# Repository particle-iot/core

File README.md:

The Spark Core
=====

These are the hardware design files for the Spark Core, developed by Hex Labs, Inc. dba Spark.

These files have been made available online through a [Creative Commons Attribution-ShareAlike 3.0](http://creativecommons.org/licenses/by-sa/3.0/) license.

You are welcome to distribute, remix, and use these files for commercial purposes. If you do so, please attribute the original design to Spark both on the website and on the physical packaging of the product or in the instruction manual. All derivative works must be published under the same or a similar license.

## The Story

Development of the Spark Core in its current form began in January 2013 in Shenzhen, China during Spark's participation in the HAXLR8R hardware accelerator.  Development of the Spark Cloud was started in December 2011 as software infrastructure to support the Spark Socket.  Between January and May of 2013, the Spark Core and Cloud were developed from prototypes to a functional platform for building internet-connected hardware.  On May 2, 2013, the Spark Core was launched on the crowdfunding platform Kickstarter.  On May 17, 2013, the hardware design files for the product were released here on GitHub for others to use and learn from.

## What's Included

**BOM** — Current bill of materials for the latestversion of the Spark Core.  Includes part number labels from design files, component values, quantities, and package types.

**Datasheets** — Datasheets for the various components included on the Spark Core, including the STM32F103CBT6 microcontroller and the CC3000 Wi-Fi module.

**EAGLE** — Schematic and board files for the Spark Core.  We use EAGLE, a freemium PCB design software package, for the design and development of the Spark Core.

**Gerber** — Complete set of Gerber files for the current version of the Core.  Use these files to spin up and assemble your own Cores!

**Libraries** — EAGLE libraries for the components used on the Spark Core.

**PDFs** — Includes detailed description of component placement on the Core (especially useful during assembly).  Also includes mechanical drawings and a detailed schematic of the Core for reference and debugging.

**Pin Mapping** — Detailed pin mapping of the Spark Core and STM32, providing information about which pins are mapped to which peripherals.

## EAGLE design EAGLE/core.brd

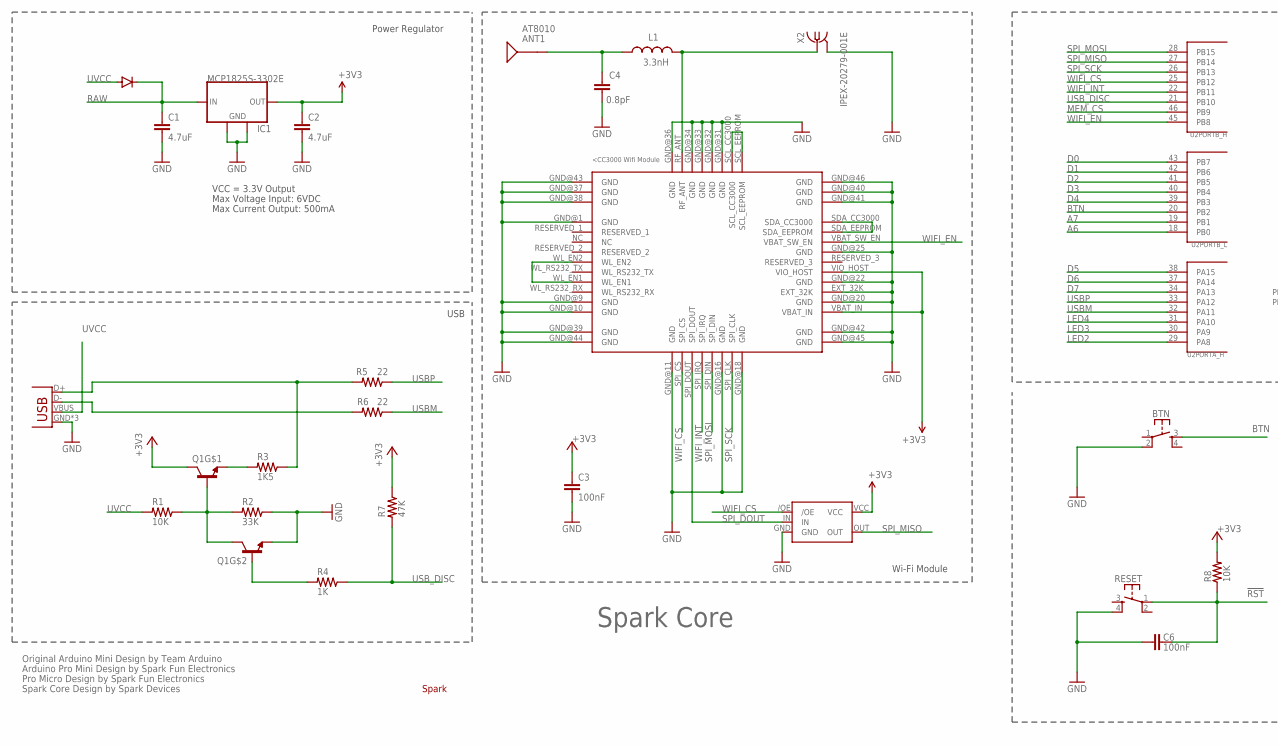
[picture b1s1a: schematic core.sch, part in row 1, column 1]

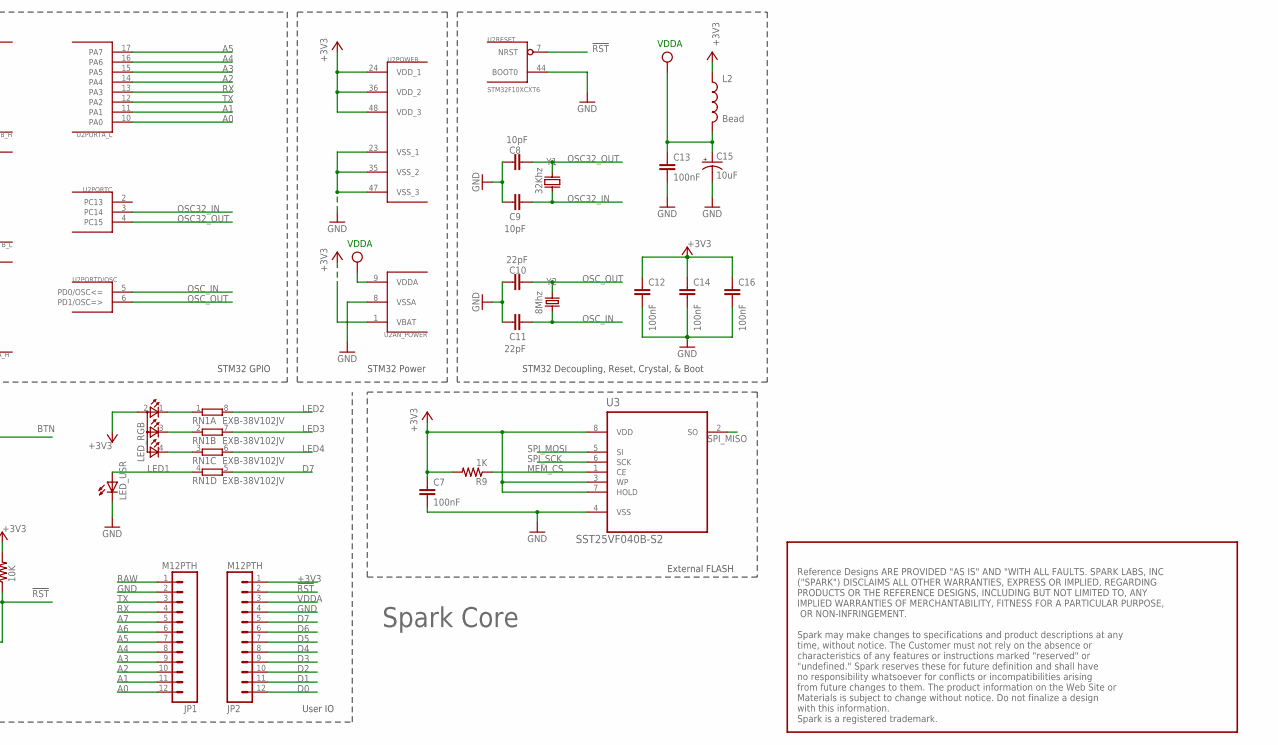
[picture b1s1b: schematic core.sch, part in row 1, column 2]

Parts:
ANT1: AT8010
BTN: KMR211GLFS; TACTILE_SWITCH_SMD
C1, C2: 4.7uF; C0603
C3, C6, C7, C12, C13, C14, C16: 100nF; C0603
C4: 0.8pF; C0603
C8, C9: 10pF; C0603
C10, C11: 22pF; C0603
C15: 10uF; EIA3216
D1: DIODE; DIODE-DO-220AA(SMP)
IC1: MCP1825S-3302E; SOT223
JP1, JP2: M12PTH; 1X12-SMALL-PADS
L1: 3.3nH; 0603
L2: Bead; 0603
LED_RGB: TOPLED-3PLCC; P-LCC-4-3
LED_USR: LED0603; LED-0603
Q1: MMDT3904; SOT363
R1, R8: 10K; R0603
R2: 33K; R0603
R3: 1K5; R0603
R4, R9: 1K; R0603
R5, R6: 22; R0603
R7: 47K; R0603
RESET: KMR211GLFS; TACTILE_SWITCH_SMD
RN1: EXB-38V102JV; EXB38V
U1: CC3000
U2: STM32F10XCXT6; TQFP48
U3: SST25VF040B-S2; SOIC127P790X216-8N
U4: NL17SZ125SOT553; SOT-553
U$1: SPARK_LOGO2
X1: USB-MICROB; USB-MICROB-SLOT-HOLE
X2: IPEX-20279-001E
Y1: 32Khz; FC135
Y2: 8Mhz; CRYSTAL-SMD-5X3

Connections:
!RST: C6.2, JP2.2, R8.1, RESET.1, U2.7 (NRST)
+3V3: C2.1, C3.1, C7.1, C12.1, C14.1, C16.1, IC1.3 (OUT), JP2.1, L2.1, LED_RGB.2 (A2), Q1.3 (C), R7.1, R8.2, R9.2, U1.VBAT_IN, U1.VIO_HOST, U2.1 (VBAT), U2.24 (VDD_1), U2.36 (VDD_2), U2.48 (VDD_3), U3.3 (WP), U3.7 (HOLD), U3.8 (VDD), U4.VCC
A0: JP1.12, U2.10 (PA0)
A1: JP1.11, U2.11 (PA1)
A2: JP1.10, U2.14 (PA4)
A3: JP1.9, U2.15 (PA5)
A4: JP1.8, U2.16 (PA6)
A5: JP1.7, U2.17 (PA7)
A6: JP1.6, U2.18 (PB0)
A7: JP1.5, U2.19 (PB1)
BTN: BTN.3, U2.20 (PB2)
D0: JP2.12, U2.43 (PB7)
D1: JP2.11, U2.42 (PB6)
D2: JP2.10, U2.41 (PB5)
D3: JP2.9, U2.40 (PB4)
D4: JP2.8, U2.39 (PB3)
D5: JP2.7, U2.38 (PA15)
D6: JP2.6, U2.37 (PA14)
D7: JP2.5, RN1.5 (2), U2.34 (PA13)
GND: BTN.2, C1.2, C2.2, C3.2, C4.2, C6.1, C7.2, C8.2, C9.2, C10.2, C11.2, C12.2, C13.2, C14.2, C15.C (-), C16.2, IC1.2 (GND), IC1.4 (GND), JP1.2, JP2.4, LED_USR.C, Q1.1 (E), R2.1, RESET.4, U1.EXT_32K, U1.GND@1 (GND), U1.GND@9 (GND), U1.GND@10 (GND), U1.GND@11 (GND), U1.GND@16 (GND), U1.GND@18 (GND), U1.GND@20 (GND), U1.GND@22 (GND), U1.GND@25 (GND), U1.GND@31 (GND), U1.GND@32 (GND), U1.GND@33 (GND), U1.GND@34 (GND), U1.GND@36 (GND), U1.GND@37 (GND), U1.GND@38 (GND), U1.GND@39 (GND), U1.GND@40 (GND), U1.GND@41 (GND), U1.GND@42 (GND), U1.GND@43 (GND), U1.GND@44 (GND), U1.GND@45 (GND), U1.GND@46 (GND), U2.8 (VSSA), U2.23 (VSS_1), U2.35 (VSS_2), U2.44 (BOOT0), U2.47 (VSS_3), U3.4 (VSS), U4.GND, X1.GND, X1.MT1 (GND), X1.MT2 (GND), X2.2@1 (GND), X2.2@2 (GND)
LED1: LED_USR.A, RN1.4 (1)
LED2: RN1.8 (2), U2.29 (PA8)
LED3: RN1.7 (2), U2.30 (PA9)
LED4: RN1.6 (2), U2.31 (PA10)
MEM_CS: R9.1, U2.46 (PB9), U3.1 (CE)
unnamed: R3.1, R5.2, X1.D+
unnamed: L1.2, U1.RF_ANT, X2.1
unnamed: ANT1.SIG, C4.1, L1.1
unnamed: R6.2, X1.D-
unnamed: U1.SCL_CC3000, U1.SCL_EEPROM
unnamed: Q1.2 (B), R4.2
unnamed: U1.WL_EN1, U1.WL_EN2
unnamed: LED_RGB.1 (CRED), RN1.1
unnamed: LED_RGB.3 (CBLUE), RN1.2 (1)
unnamed: Q1.5 (B), Q1.6 (C), R1.1, R2.2
unnamed: LED_RGB.4 (CGREEN), RN1.3 (1)
unnamed: U1.SDA_CC3000, U1.SDA_EEPROM
unnamed: Q1.4 (E), R3.2
OSC32_IN: C9.1, U2.3 (PC14), Y1.X1 (1)
OSC32_OUT: C8.1, U2.4 (PC15), Y1.X2 (2)
OSC_IN: C11.1, U2.5 (PD0/OSC<=), Y2.1
OSC_OUT: C10.1, U2.6 (PD1/OSC=>), Y2.3 (2)
RAW: C1.1, D1.CATHODE, IC1.1 (IN), JP1.1
RX: JP1.4, U2.13 (PA3)
SPI_DOUT: U1.SPI_DOUT, U4.IN
SPI_MISO: U2.27 (PB14), U3.2 (SO), U4.OUT
SPI_MOSI: U1.SPI_DIN, U2.28 (PB15), U3.5 (SI)
SPI_SCK: U1.SPI_CLK, U2.26 (PB13), U3.6 (SCK)
TX: JP1.3, U2.12 (PA2)
USBM: R6.1, U2.32 (PA11)
USBP: R5.1, U2.33 (PA12)
USB_DISC: R4.1, R7.2, U2.21 (PB10)
UVCC: D1.ANODE, R1.2, X1.VBUS
VDDA: C13.1, C15.A (+), JP2.3, L2.2, U2.9 (VDDA)
WIFI_CS: U1.SPI_CS, U2.25 (PB12), U4./OE
WIFI_EN: U1.VBAT_SW_EN, U2.45 (PB8)
WIFI_INT: U1.SPI_IRQ, U2.22 (PB11)

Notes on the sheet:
Original Arduino Mini Design by Team Arduino
Arduino Pro Mini Design by Spark Fun Electronics
Max Voltage Input: 6VDC
Max Current Output: 500mA
Power Regulator
VCC = 3.3V Output
Pro Micro Design by Spark Fun Electronics
Spark Core Design by Spark Devices
STM32 Decoupling, Reset, Crystal, & Boot
STM32 GPIO
STM32 Power
External FLASH
User IO
USB
Spark Core
Wi-Fi Module
VDDA
Reference Designs ARE PROVIDED "AS IS" AND "WITH ALL FAULTS. SPARK LABS, INC ("SPARK") DISCLAIMS ALL OTHER WARRANTIES, EXPRESS OR IMPLIED, REGARDING PRODUCTS OR THE REFERENCE DESIGNS, INCLUDING BUT NOT LIMITED TO, ANY IMPLIED WARRANTIES OF MERCHANTABILITY, FITNESS FOR A PARTICULAR PURPOSE, OR NON-I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

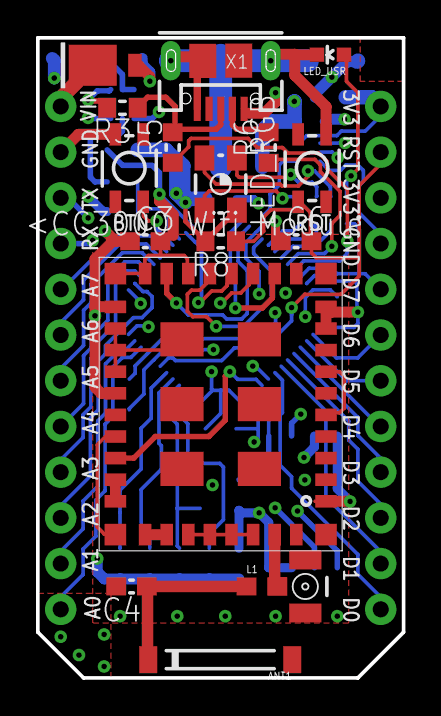
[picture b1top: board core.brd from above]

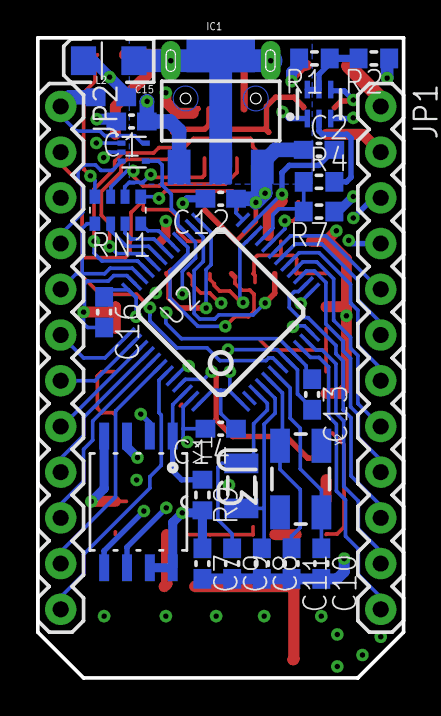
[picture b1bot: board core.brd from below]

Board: 4 copper layers, 20.3 x 35.6 mm, 46 parts (28 on the bottom side), 57 nets.

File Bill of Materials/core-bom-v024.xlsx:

| LAST UPDATED |  | 41508
 | SPARK CORE
 | Qty | Device | Minimum Specification | Component Value (if different) | Package/Case | Designator | AVL | AVL P/N | Additional Comments
 | 1 | Fab PCB | FR4, 1.6mm, 1OZ, Electroless Nickel Immersion Gold, White Solder Mask, Black Si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
 | 7 | Ceramic Capacitor | 100nF, Ceramic, 10V, 10%, X5R | 25V, X7R | 0603 | C3, C6-7, C12-14, C16 | Yageo | CC0603KRX7R8BB104
 | 2 | Ceramic Capacitor | 10pF, Ceramic, 10V, 10%, X5R |  | 0603 | C8, C9
 | 2 | Ceramic Capacitor | 22pF, Ceramic, 10V, 10%, X5R | 50V, 5% | 0603 | C10, C11 | Yageo | CC0603JRNPO9BN220
 | 2 | Ceramic Capacitor | 4.7uF, Ceramic, 10V, 10%, X5R |  | 0603 | C1, C2 | Samsung Electro-Mechanics | CL10A475KP8NNNC
 | 1 | Ceramic RF Capacitor | 10pF, Ceramic, 25V, 5% | 250V | 0603 | C5 | Johanson Technology Inc | 251R14S100JV4T | Must be RF capacitor
 | 1 | Ceramic RF Capacitor | 2.2pF, Ceramic, 25V, ±0.25pF | 250V, ±0.1pF | 0603 | C4 | Johanson Technology Inc | 251R14S2R2BV4T | Must be RF capacitor
 | 1 | Chip Antenna | 2.4GHz, Ceramic |  | 8mm x 1mm | A1 | ACX | US PN = 2500AT44M0400E Asia PN = AT8010-E2R9HAA
 | 1 | Chip Resistor Array | 1K, 1/4W, 4 Resistors, 5% | 62.5mW per element | 1206 | RN1 | Panasonic Electric Components | EXB-38V102JV
 | 1 | Crystal | 8MHz Crystal, 18pF, SMD |  | 5032 | Y2 | Song Ji | SMD5032 4P 30M | 4 pads
 | 1 | Diode | 30V, 3A |  | DO-220AA | D1 | Vishay | SS3P3-M3/84A
 | 1 | RF Inductor | 2.2nH, Ceramic |  | 0603 | L1 | TDK | MLG1608B2N2S | Must be RF inductor
 | 1 | Dual NPN transistor | Dual NPN, 40V |  | SOT363 | Q1 | Micro Commercial Co | MMDT3904-TP
 | 1 | Ferrite bead | 220Ω, 500mA |  | 0603 | L2 | Murata | BLM18AG221SN1D
 | 2 | Header | Single String, 0.230" Mating Length |  | 0.1", 12 pin | JP1, JP2 | Kaweei | CP25411-12G-S116-A
 | 1 | LED | Blue, SMD |  | 0603 | LED1 | Wenliang | WLUB0603A-341
 | 1 | Microcontroller | MCU ARM 128K, 48-pin |  | LQFP48 | U3 | STMicroelectronics | STM32F103CBT6
 | 2 | Resistor | 10K, 1/10W, 5% |  | 0603 | R1, R8 | Vishay | CRCW060310K0JNEB
 | 2 | Resistor | 22Ω, 1/10W, 5% |  | 0603 | R5, R6 | Yageo | RC0603JR-0722RL
 | 2 | Resistor | 1K, 1/10W, 5% |  | 0603 | R4, R9 | Vishay | CRCW06031K00JNEA
 | 1 | Resistor | 33K, 1/10W, 5% |  | 0603 | R2 | Vishay | CRCW060333K0JNEB
 | 1 | Resistor | 1K5, 1/10W, 5% |  | 0603 | R3 | Vishay | CRCW06031K50JNEA
 | 1 | Resistor | 47K, 1/10W, 5% |  | 0603 | R7 | Vishay | CRCW060347K0JNEB
 | 1 | RGB LED | 3528 RGB LED |  | 3528 | LED2 | Wenliang | WLRGB3528C/R
 | 1 | RTC Crystal | 32.768KHz, 7pF RTC Crystal |  | 2-SMD | Y1 | Song Ji | SJFC1332K07P20
 | 1 | SPI Flash Module | 16Mbit, 75MHz |  | 8-SOIC | U3 | Microchip Technology | SST25VF016B-75-4I-S2AF-T
 | 2 | Tactile Switch | Button, 160gf |  | 3.6mm x 3.1mm | B1, B2 | Haoyu | TS-1185A-C
 | 1 | Tantalum Capacitor | 10uF, Tantalum, 10V, 20% |  | 1206 | C16 | AVX | TAJA106M010RNJ
 | 1 | uFL Connector | IPEX-20279-001E |  | SMD | X2 | Kaweei | P1163-0140R
 | 1 | USB Micro B Connector | USB Micro B, SMT with TH Board Guides |  | USB-MICROB | X1 | Kaweei | CMCUSB-5BFM2G-01-D
 | 1 | Voltage Regulator | 3.3V, 0.5A LDO |  | SOT223 | U1 | Microchip Technology | MCP1825S-3302E/DB
 | 1 | Wi-Fi Module | Wi-Fi Module |  |  | U2 | Texas Instruments | CC3000
 | 1 | Buffer | Non-inverting 3-state buffer |  | SOT553 | U4 | ON Semiconductor | NL17SZ125 | Many other manufacturers available
 | ACCESSORIES
 | Qty | Device | Minimum Specification | Component Value (if different) | Package/Case | Designator | AVL | AVL P/N | Additional Comments
 | 1 | Mini Breadboard | Transparent, 400pt or smaller |  | 3.5 x 4.5cm
 | 1 | USB Micro - B Cable | 1m Flat, Black |  | USB-MICROB
 | PACKAGING
 | Qty | Device | Minimum Specification | Component Value (if different) | Package/Case | Designator | AVL | AVL P/N | Additional Comments
 | 1 | Core Box | 1-C, Cardboard, Double-sided
 | 1 | Static Sponge

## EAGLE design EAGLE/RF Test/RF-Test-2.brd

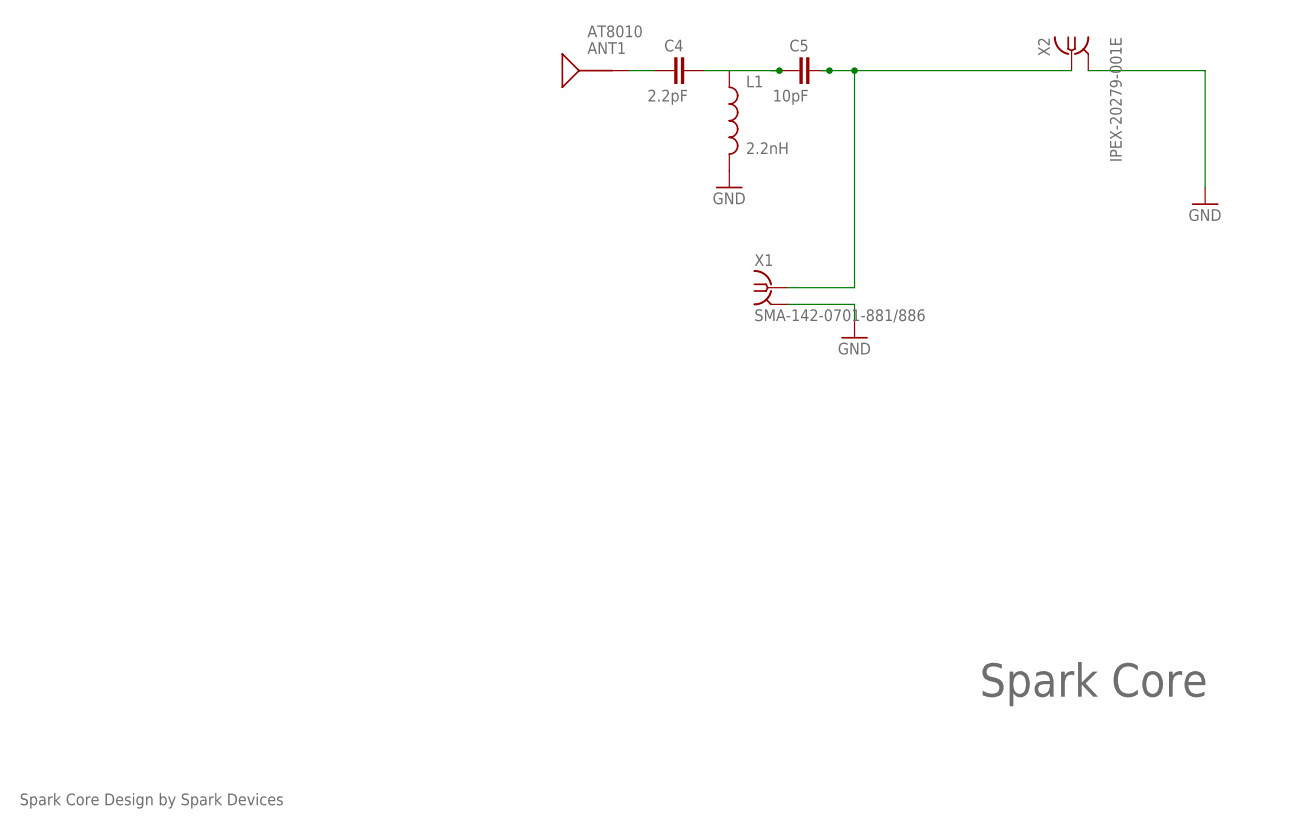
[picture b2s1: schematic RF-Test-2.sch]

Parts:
ANT1: AT8010
C4: 2.2pF; C0603
C5: 10pF; C0603
L1: 2.2nH; 0603
X1: SMA-142-0701-881/886; ANDYW-GENERIC-END-LAUNCH
X2: IPEX-20279-001E

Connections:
GND: L1.2, X1.G@1 (2), X1.G@2 (2), X1.G@3 (2), X1.G@4 (2), X2.2@1 (GND), X2.2@2 (GND)
unnamed: ANT1.SIG, C4.1
unnamed: C5.2, X1.1, X2.1
unnamed: C4.2, C5.1, L1.1

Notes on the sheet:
Spark Core Design by Spark Devices
Spark Core

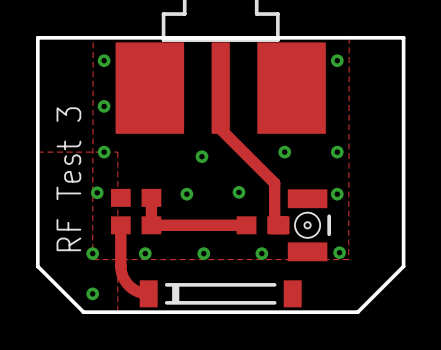
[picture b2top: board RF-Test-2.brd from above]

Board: 4 copper layers, 20.3 x 15.2 mm, 6 parts (0 on the bottom side), 4 nets.

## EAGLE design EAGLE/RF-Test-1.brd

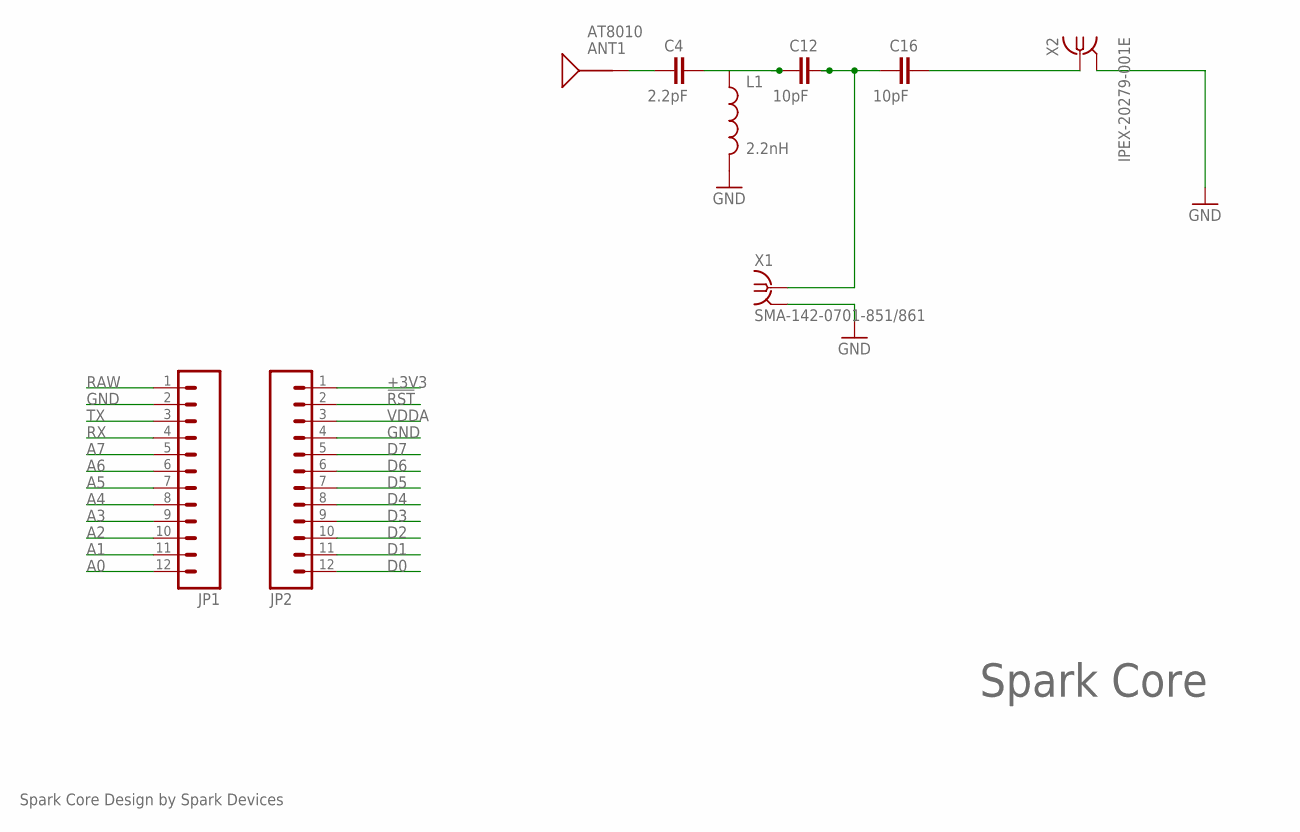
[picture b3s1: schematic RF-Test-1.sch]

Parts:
ANT1: AT8010
C4: 2.2pF; C0603
C12, C16: 10pF; C0603
JP1, JP2: M12PTH; 1X12
L1: 2.2nH; 0603
X1: SMA-142-0701-851/861; J502-ND-142-0701-851/861
X2: IPEX-20279-001E

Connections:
!RST: JP2.2
+3V3: JP2.1
A0: JP1.12
A1: JP1.11
A2: JP1.10
A3: JP1.9
A4: JP1.8
A5: JP1.7
A6: JP1.6
A7: JP1.5
D0: JP2.12
D1: JP2.11
D2: JP2.10
D3: JP2.9
D4: JP2.8
D5: JP2.7
D6: JP2.6
D7: JP2.5
GND: JP1.2, JP2.4, L1.2, X1.G@1 (2), X1.G@2 (2), X1.G@3 (2), X1.G@4 (2), X2.2@1 (GND), X2.2@2 (GND)
unnamed: C16.2, X2.1
unnamed: ANT1.SIG, C4.1
unnamed: C12.2, C16.1, X1.1
unnamed: C4.2, C12.1, L1.1
RAW: JP1.1
RX: JP1.4
TX: JP1.3
VDDA: JP2.3

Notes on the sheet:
Spark Core Design by Spark Devices
Spark Core

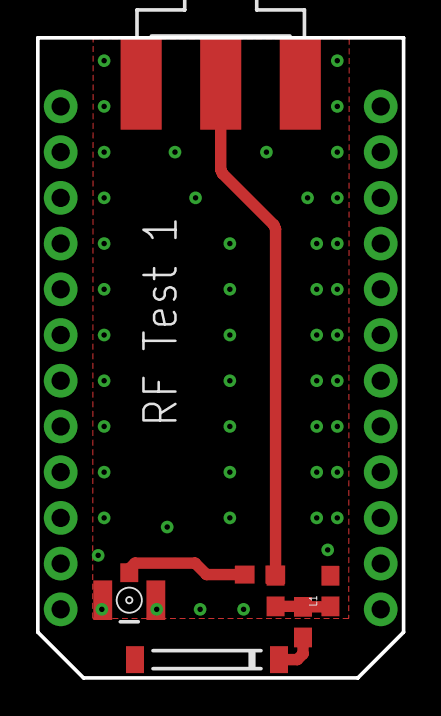
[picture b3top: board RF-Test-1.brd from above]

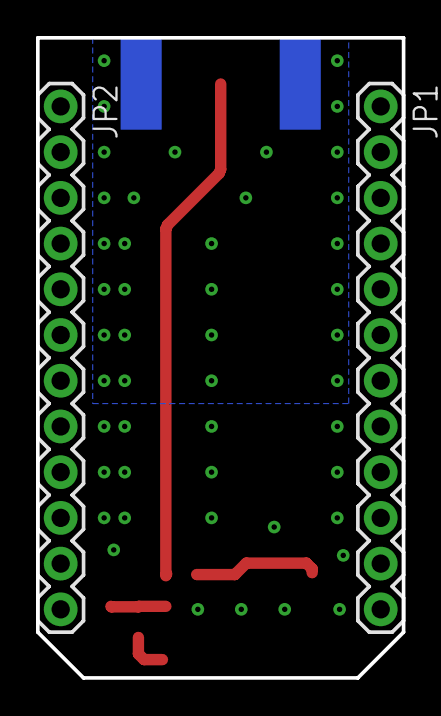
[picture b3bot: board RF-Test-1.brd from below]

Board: 4 copper layers, 20.3 x 35.6 mm, 9 parts (2 on the bottom side), 5 nets.

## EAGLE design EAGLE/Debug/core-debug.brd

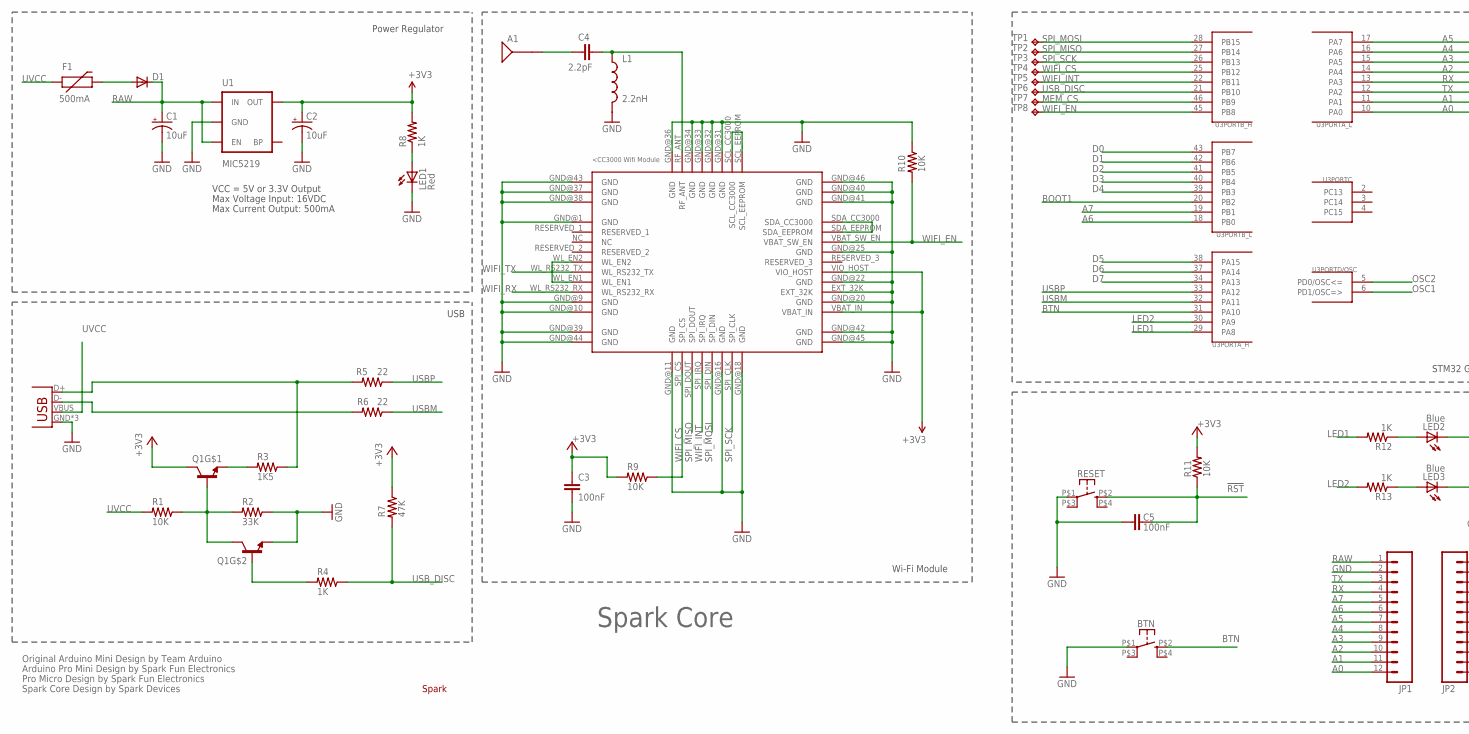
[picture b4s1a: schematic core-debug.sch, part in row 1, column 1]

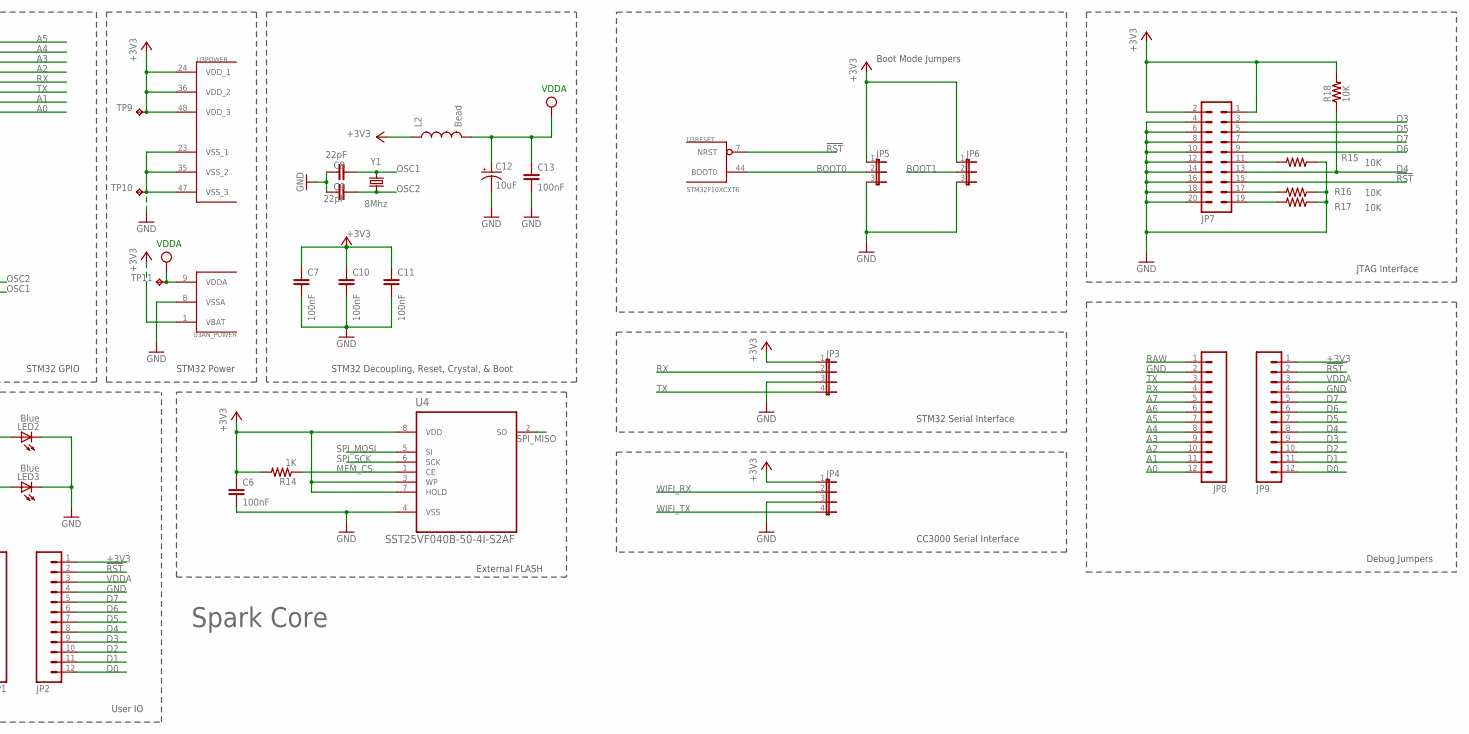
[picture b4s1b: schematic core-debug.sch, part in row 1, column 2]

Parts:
A1: ANTENNA2SMD5; ANTENNA-CHIP5
BTN: KMR211GLFS; PUSHBUTTON-KMR241GLFS
C1, C2, C12: 10uF; EIA3216
C3, C5, C6, C7, C10, C11, C13: 100nF; C0603
C4: 2.2pF; C0603
C8, C9: 22pF; C0603
D1: DIODESOD; SOD-323
F1: 500mA; PTC-1206
JP1, JP2, JP8, JP9: M12PTH; 1X12
JP3, JP4: JP4E; JP4
JP5, JP6: JP2E; JP2
JP7: ML20
L1: 2.2nH; 0603
L2: Bead; 0603
LED1: Red; LED-0603
LED2, LED3: Blue; LED-0603
Q1: MMDT3904; SOT363
R1, R9, R10, R11, R15, R16, R17, R18: 10K; R0603
R2: 33K; R0603
R3: 1K5; R0603
R4, R8, R12, R13, R14: 1K; R0603
R5, R6: 22; R0603
R7: 47K; R0603
RESET: KMR211GLFS; PUSHBUTTON-KMR241GLFS
TP1, TP2, TP3, TP4, TP5, TP6, TP7, TP8, TP9, TP10, TP11: TPPAD1-17; P1-17
U1: MIC5219; SOT23-5
U2: CC3000
U3: STM32F10XCXT6; TQFP48
U4: SST25VF040B-50-4I-S2AF; SOIC127P790X216-8N
U$1: SPARK_LOGO2
X1: USB-MICROB
Y1: 8Mhz; CRYSTAL-SMD-5X3

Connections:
!RST: C5.2, JP2.2, JP7.15, JP9.2, R11.1, RESET.P$2 (2), U3.7 (NRST)
+3V3: C2.A (+), C3.1, C6.1, C7.1, C10.1, C11.1, JP2.1, JP3.1, JP4.1, JP5.1, JP6.1, JP7.1, JP7.2, JP9.1, L2.1, Q1.3 (C), R7.1, R8.2, R9.2, R11.2, R14.2, R18.2, TP9.TP, U1.5 (OUT), U2.VBAT_IN, U2.VIO_HOST, U3.1 (VBAT), U3.24 (VDD_1), U3.36 (VDD_2), U3.48 (VDD_3), U4.3 (WP), U4.7 (HOLD), U4.8 (VDD)
A0: JP1.12, JP8.12, U3.10 (PA0)
A1: JP1.11, JP8.11, U3.11 (PA1)
A2: JP1.10, JP8.10, U3.14 (PA4)
A3: JP1.9, JP8.9, U3.15 (PA5)
A4: JP1.8, JP8.8, U3.16 (PA6)
A5: JP1.7, JP8.7, U3.17 (PA7)
A6: JP1.6, JP8.6, U3.18 (PB0)
A7: JP1.5, JP8.5, U3.19 (PB1)
BOOT0: JP5.2, U3.44 (BOOT0)
BOOT1: JP6.2, U3.20 (PB2)
BTN: BTN.P$2 (2), U3.31 (PA10)
D0: JP2.12, JP9.12, U3.43 (PB7)
D1: JP2.11, JP9.11, U3.42 (PB6)
D2: JP2.10, JP9.10, U3.41 (PB5)
D3: JP2.9, JP7.3, JP9.9, U3.40 (PB4)
D4: JP2.8, JP7.13, JP9.8, R18.1, U3.39 (PB3)
D5: JP2.7, JP7.5, JP9.7, U3.38 (PA15)
D6: JP2.6, JP7.9, JP9.6, U3.37 (PA14)
D7: JP2.5, JP7.7, JP9.5, U3.34 (PA13)
GND: BTN.P$1 (1), C1.C (-), C2.C (-), C3.2, C5.1, C6.2, C7.2, C8.2, C9.2, C10.2, C11.2, C12.C (-), C13.2, JP1.2, JP2.4, JP3.3, JP4.3, JP5.3, JP6.3, JP7.4, JP7.6, JP7.8, JP7.10, JP7.12, JP7.14, JP7.16, JP7.18, JP7.20, JP8.2, JP9.4, L1.2, LED1.C, LED2.C, LED3.C, Q1.1 (E), R2.1, R10.1, R15.1, R16.1, R17.1, RESET.P$1 (1), TP10.TP, U1.2 (GND), U2.EXT_32K, U2.GND@1 (GND), U2.GND@9 (GND), U2.GND@10 (GND), U2.GND@11 (GND), U2.GND@16 (GND), U2.GND@18 (GND), U2.GND@20 (GND), U2.GND@22 (GND), U2.GND@25 (GND), U2.GND@31 (GND), U2.GND@32 (GND), U2.GND@33 (GND), U2.GND@34 (GND), U2.GND@36 (GND), U2.GND@37 (GND), U2.GND@38 (GND), U2.GND@39 (GND), U2.GND@40 (GND), U2.GND@41 (GND), U2.GND@42 (GND), U2.GND@43 (GND), U2.GND@44 (GND), U2.GND@45 (GND), U2.GND@46 (GND), U3.8 (VSSA), U3.23 (VSS_1), U3.35 (VSS_2), U3.47 (VSS_3), U4.4 (VSS), X1.GND, X1.MT1 (GND), X1.MT2 (GND)
LED1: R12.2, U3.29 (PA8)
LED2: R13.2, U3.30 (PA9)
MEM_CS: R14.1, TP7.TP, U3.46 (PB9), U4.1 (CE)
unnamed: R3.1, R5.2, X1.D+
unnamed: LED2.A, R12.1
unnamed: D1.2 (A), F1.2
unnamed: C4.2, L1.1, U2.RF_ANT
unnamed: A1.FEED, C4.1
unnamed: R6.2, X1.D-
unnamed: U2.SCL_CC3000, U2.SCL_EEPROM
unnamed: Q1.2 (B), R4.2
unnamed: U2.WL_EN1, U2.WL_EN2
unnamed: LED3.A, R13.1
unnamed: JP7.19, R17.2
unnamed: JP7.11, R15.2
unnamed: Q1.5 (B), Q1.6 (C), R1.1, R2.2
unnamed: JP7.17, R16.2
unnamed: U2.SDA_CC3000, U2.SDA_EEPROM
unnamed: Q1.4 (E), R3.2
unnamed: LED1.A, R8.1
OSC1: C8.1, U3.6 (PD1/OSC=>), Y1.3 (2)
OSC2: C9.1, U3.5 (PD0/OSC<=), Y1.1
RAW: C1.A (+), D1.1 (C), JP1.1, JP8.1, U1.1 (IN), U1.3 (EN)
RX: JP1.4, JP3.2, JP8.4, U3.13 (PA3)
SPI_MISO: TP2.TP, U2.SPI_DOUT, U3.27 (PB14), U4.2 (SO)
SPI_MOSI: TP1.TP, U2.SPI_DIN, U3.28 (PB15), U4.5 (SI)
SPI_SCK: TP3.TP, U2.SPI_CLK, U3.26 (PB13), U4.6 (SCK)
TX: JP1.3, JP3.4, JP8.3, U3.12 (PA2)
USBM: R6.1, U3.32 (PA11)
USBP: R5.1, U3.33 (PA12)
USB_DISC: R4.1, R7.2, TP6.TP, U3.21 (PB10)
UVCC: F1.1, R1.2, X1.VBUS
VDDA: C12.A (+), C13.1, JP2.3, JP9.3, L2.2, TP11.TP, U3.9 (VDDA)
WIFI_CS: R9.1, TP4.TP, U2.SPI_CS, U3.25 (PB12)
WIFI_EN: R10.2, TP8.TP, U2.VBAT_SW_EN, U3.45 (PB8)
WIFI_INT: TP5.TP, U2.SPI_IRQ, U3.22 (PB11)
WIFI_RX: JP4.2, U2.WL_RS232_RX
WIFI_TX: JP4.4, U2.WL_RS232_TX

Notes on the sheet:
Original Arduino Mini Design by Team Arduino
Arduino Pro Mini Design by Spark Fun Electronics
Max Voltage Input: 16VDC
Max Current Output: 500mA
Power Regulator
VCC = 5V or 3.3V Output
Pro Micro Design by Spark Fun Electronics
Spark Core Design by Spark Devices
STM32 Decoupling, Reset, Crystal, & Boot
STM32 GPIO
STM32 Power
External FLASH
User IO
USB
Spark Core
Wi-Fi Module
VDDA
Boot Mode Jumpers
STM32 Serial Interface
JTAG Interface
CC3000 Serial Interface
Debug Jumpers

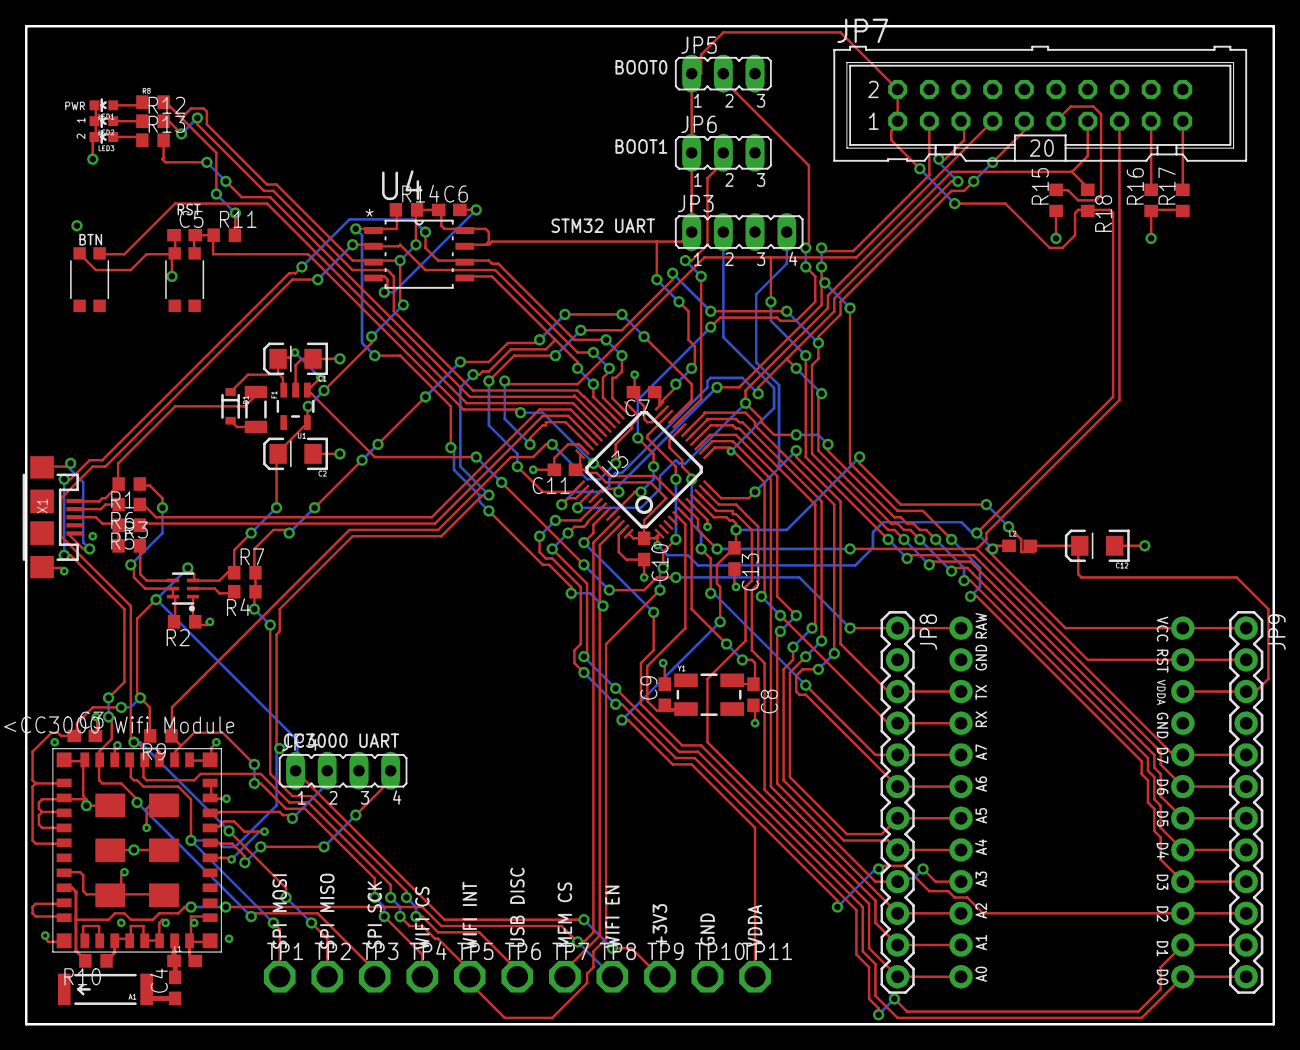
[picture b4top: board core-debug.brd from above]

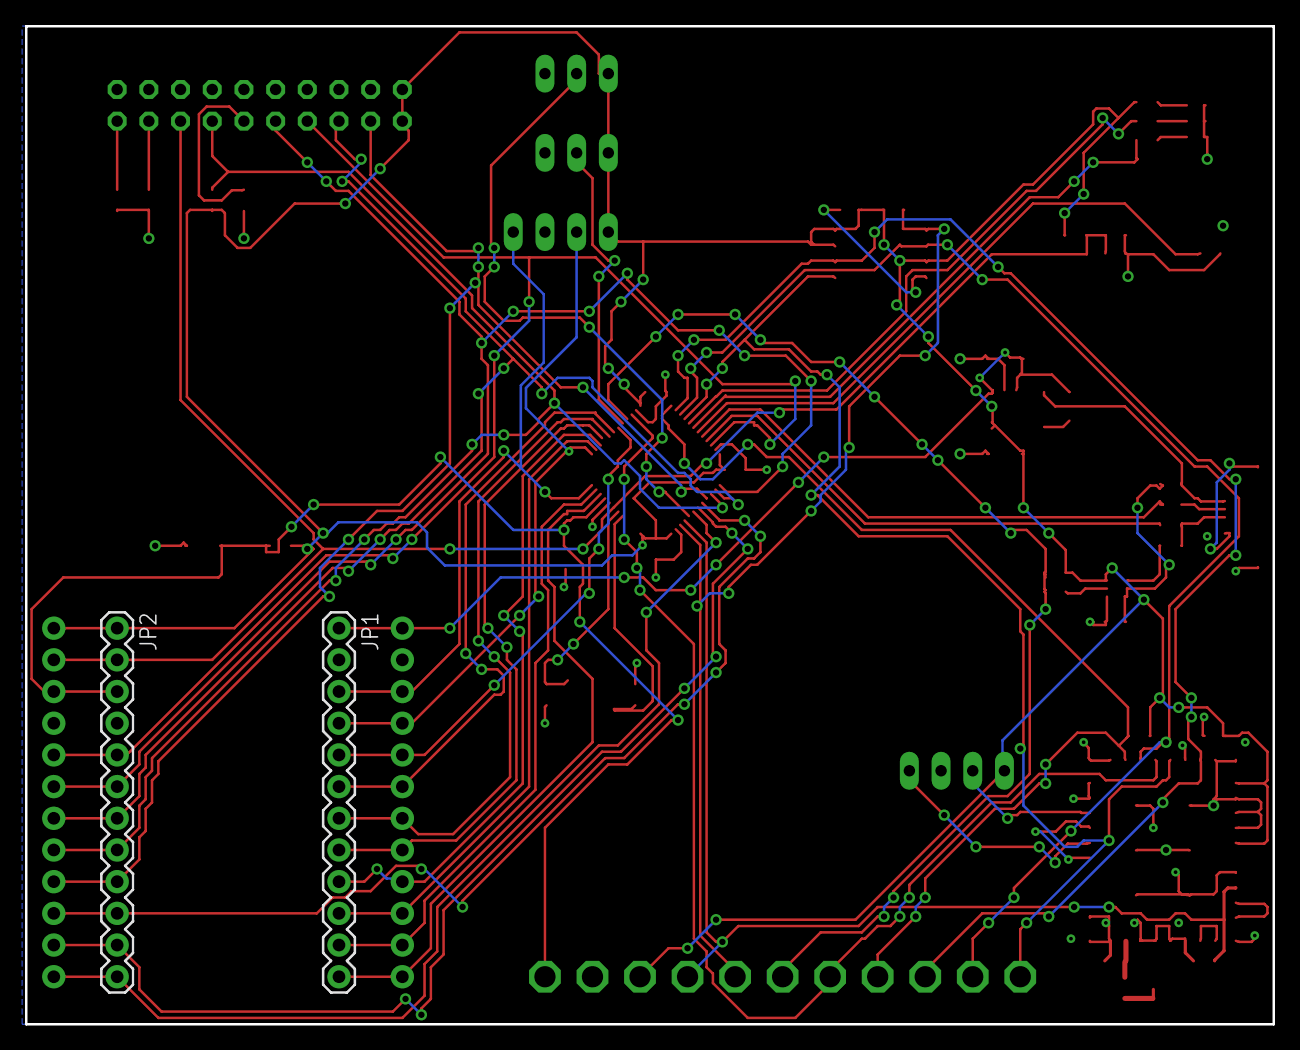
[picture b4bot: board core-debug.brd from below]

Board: 2 copper layers, 100.0 x 80.0 mm, 69 parts (2 on the bottom side), 60 nets.

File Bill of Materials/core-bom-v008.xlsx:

Part | Value | Device | Package | DigiKey Link | Taobao Link | Quantity | Status | Price (CNY) | Price (USD) | Total Price (USD)
A1 | 2.4Ghz ceramic | Chip antenna | 6.5mm x 2.8mm |  | http://item.taobao.com/item.htm?spm=a230r.1.14.59.xxVeAY&id=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 | 1 | Have | 2 | 0.32372936225315635 | 0.32372936225315635
B1, B2 | KMR211GLFS | Tactile Switch | 4.6mm x 2.8mm | http://www.digikey.com/product-detail/en/KMR211GLFS/401-1426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 | http://item.taobao.com/item.htm?spm=a230r.1.14.34.tpoElm&id=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 | 2 | Have | 2.5 | 0.40466170281644548 | 0.80932340563289096
C1, C2, C12 | 10uF | Tantalum Capacitor | 1206 |  | http://item.taobao.com/item.htm?spm=a230r.1.14.29.on1ODT&id=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 | 3 | Have | 0.3 | 4.8559404337973455E-2 | 0.14567821301392037
C3, C5-7, C10-11, C13 | 100nF | Ceramic Capacitor | 0603 |  |  | 7 | Need | 0.06 | 9.7118808675946914E-3 | 6.7983166073162835E-2
C4 | 2.2pF | Ceramic Capacitor | 0603 |  |  | 1 | Need | 0.06 | 9.7118808675946914E-3 | 9.7118808675946914E-3
C8, C9 | 22pF | Ceramic Capacitor | 0603 |  |  | 2 | Need | 0.06 | 9.7118808675946914E-3 | 1.9423761735189383E-2
D1 | RB551V-30 (500mA) | Diode | SOD-323 |  | http://detail.tmall.com/item.htm?spm=a230r.1.14.28.HWbOvn&id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 | 1 | Need | 0.06 | 9.7118808675946914E-3 | 9.7118808675946914E-3
F1 | 500mA | PTC Resettable Fuse | 1206 |  | http://detail.tmall.com/item.htm?spm=a230r.1.14.42.nwHrUU&id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 | 1 | Have | 0.5 | 8.0932340563289087E-2 | 8.0932340563289087E-2
JP1, JP2 |  | Header | 0.1", 12 pin |  |  | 2 | Have | 0.1 | 1.618646811265782E-2 | 3.2372936225315639E-2
L1 | 2.2nH | Inductor | 0603 |  |  | 1 | Need | 0.06 | 9.7118808675946914E-3 | 9.7118808675946914E-3
L2 | Murata BLM18AG221SN1D | Ferrite bead | 0603 |  | http://detail.tmall.com/item.htm?spm=a230r.1.14.1.mIn2bB&id=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 | 1 | Need | 0.06 | 9.7118808675946914E-3 | 9.7118808675946914E-3
LED1-3 | Blue | LEDs | 0603 |  | http://item.taobao.com/item.htm?spm=2013.1.w3956858894.1.emT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 | 3 | Need | 7.4999999999999997E-2 | 1.2139851084493364E-2 | 3.6419553253480091E-2
Q1 | MMDT3904 | Dual NPN transistor | SOT363 |  | http://item.taobao.com/item.htm?spm=a230r.1.14.1.JxpGm6&id=2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 | 1 | Have | 0.15 | 2.4279702168986728E-2 | 2.4279702168986728E-2
R1, R9-11 | 10K | Resistor | 0603 |  |  | 4 | Need | 0.06 | 9.7118808675946914E-3 | 3.8847523470378766E-2
R2 | 33K | Resistor | 0603 |  |  | 1 | Need | 0.06 | 9.7118808675946914E-3 | 9.7118808675946914E-3
R3 | 1K5 | Resistor | 0603 |  |  | 1 | Need | 0.06 | 9.7118808675946914E-3 | 9.7118808675946914E-3
R5, R6 | 22Ω | Resistor | 0603 |  |  | 2 | Need | 0.06 | 9.7118808675946914E-3 | 1.9423761735189383E-2
R7 | 47K | Resistor | 0603 |  |  | 1 | Need | 0.06 | 9.7118808675946914E-3 | 9.7118808675946914E-3
R4, R8, R12-14 | 1K | Resistor | 0603 |  |  | 5 | Need | 0.06 | 9.7118808675946914E-3 | 4.8559404337973455E-2
U1 | MIC5219 3.3V LDO | Voltage Regulator | SOT23-5 |  | http://item.taobao.com/item.htm?spm=a230r.1.14.1.ftfZaL&id=1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 | 1 | Have | 0.8 | 0.12949174490126256 | 0.12949174490126256
U2 | CC3000 | Wi-Fi Module | Custom |  |  | 1 | Have |  | 9 | 9
U3 | STM32F103CBT6 | ST STM32F101/103 48pin LQFP | LQFP48 |  | http://item.taobao.com/item.htm?spm=a230r.1.14.1.pBjcgl&id=1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 | 1 | Have | 11.1 | 1.7966979605050177 | 1.7966979605050177
U4 | SST25VF016B 16Mbit | SPI Flash module | 8-SOIC |  | http://item.taobao.com/item.htm?spm=a230r.1.14.1.sDPMv0&id=5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 | 1 | Have | 3.25 | 0.52606021366137912 | 0.52606021366137912
X1 | USB Micro B | USB Micro B Connector | USB-MICROB |  | http://item.taobao.com/item.htm?spm=a230r.1.14.21.Zvi13g&id=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 | 1 | Have | 0.35 | 5.665263839430236E-2 | 5.665263839430236E-2
Y1 | 8Mhz | Crystal | 5mm x 3mm |  | http://item.taobao.com/item.htm?spm=a230r.1.14.62.jgHr9v&id=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 | 1 | Have | 0.88 | 0.14244091939138881 | 0.14244091939138881
 |  |  |  |  |  |  |  |  |  | 13.366299773389446

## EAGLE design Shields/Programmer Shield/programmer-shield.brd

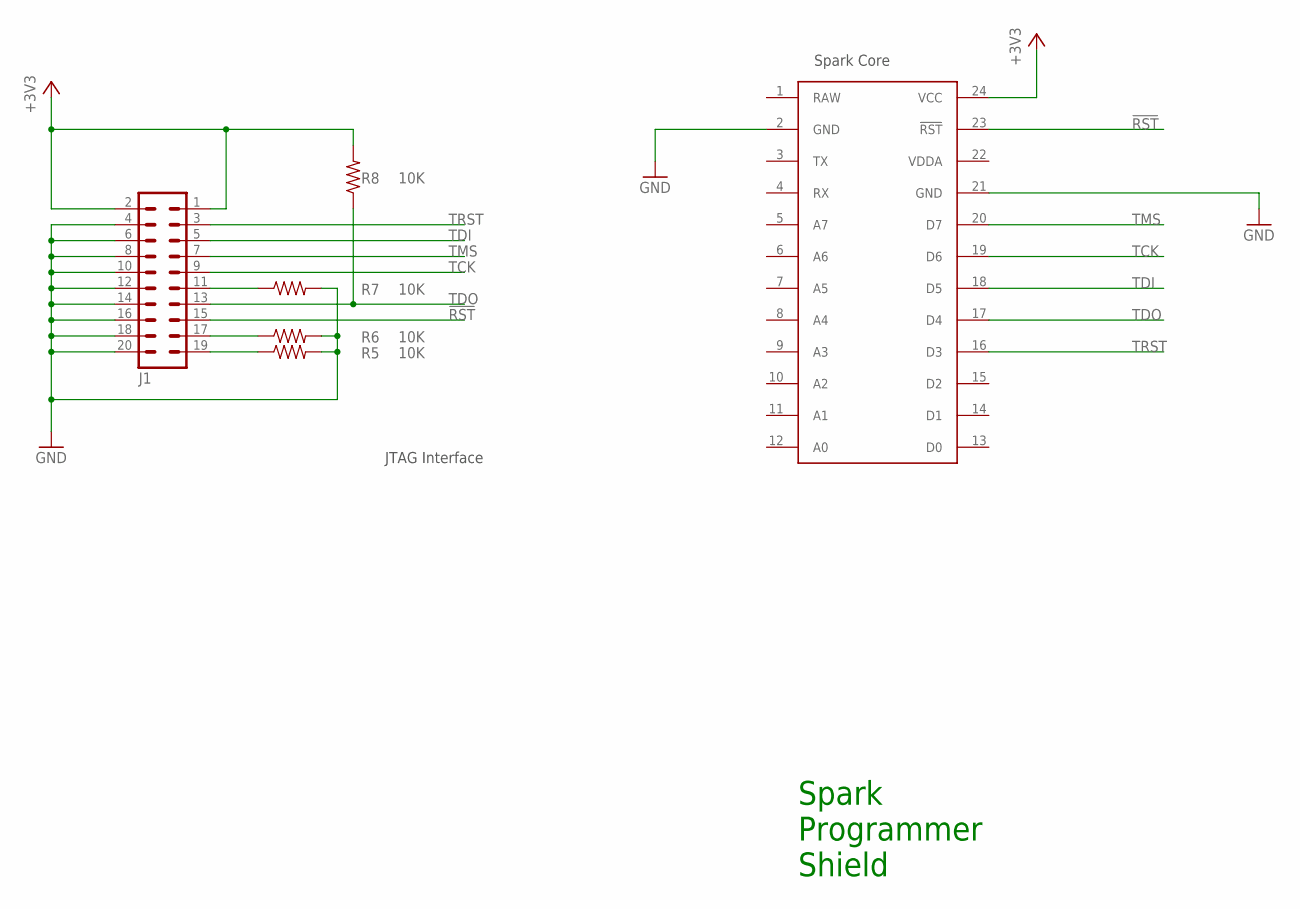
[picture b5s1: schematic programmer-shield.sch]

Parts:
J1: ML20
R5, R6, R7, R8: 10K; AXIAL-0.3
U$1: SPARK_CORECORE; SPARK_CORE

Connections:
!RST: J1.15, U$1.23 (!RST)
+3V3: J1.1, J1.2, R8.P$2 (2), U$1.24 (VCC)
GND: J1.4, J1.6, J1.8, J1.10, J1.12, J1.14, J1.16, J1.18, J1.20, R5.P$2 (2), R6.P$2 (2), R7.P$2 (2), U$1.2 (GND), U$1.21 (GND)
unnamed: J1.19, R5.P$1 (1)
unnamed: J1.17, R6.P$1 (1)
unnamed: J1.11, R7.P$1 (1)
RAW: U$1.1 (RAW)
TCK: J1.9, U$1.19 (D6)
TDI: J1.5, U$1.18 (D5)
TDO: J1.13, R8.P$1 (1), U$1.17 (D4)
TMS: J1.7, U$1.20 (D7)
TRST: J1.3, U$1.16 (D3)
VDDA: U$1.22 (VDDA)

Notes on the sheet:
JTAG Interface
Spark Core
Spark Programmer Shield

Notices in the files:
parts and their libraries:
SparkFun-RF: Licensing: CC v3.0 Share-Alike You are welcome to use this library for commercial purposes.
